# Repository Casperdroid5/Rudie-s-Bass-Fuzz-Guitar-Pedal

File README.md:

# Rudie's Bass Fuzz Guitar Pedal

The Rudie's Bass Fuzz guitar pedal is a unique effect pedal designed to add an interesting twist to the raw sound output of a guitar, particularly bass guitars. With its simple components and construction, it can be replicated for personal use and experimentation.

## Key Features

- **Distinctive Fuzz Effect:** The pedal delivers a powerful and distinctive fuzz effect that adds grit, sustain, and a rich harmonic texture to the guitar's sound. It enhances the overall tone, providing a unique character and vintage vibe to the playing experience.

- **Customizable Controls:** The pedal offers customizable controls, allowing musicians to fine-tune the fuzz effect according to their preferences. Parameters such as gain, tone, and sustain can be adjusted to achieve the desired sound and response.

- **Versatile Usage:** The Bass Fuzz pedal is not limited to bass guitars only. It can also be used with electric guitars and other stringed instruments, providing a wide range of sonic possibilities and expanding the creative options for musicians.

- **True Bypass:** The pedal features true bypass switching, ensuring that the guitar's original signal remains unaltered when the effect is disengaged. This preserves the instrument's natural tone and allows for seamless integration into any setup.

- **Rugged Construction:** The pedal is built with durability in mind. Its sturdy and compact design ensures it can withstand the rigors of live performances and studio sessions. The high-quality components used in its construction contribute to its reliability and longevity.

- **Easy to Use:** The Bass Fuzz pedal is designed for simplicity and ease of use. It features intuitive controls that musicians of all levels can quickly understand and operate. Whether you're a beginner exploring different effects or an experienced player, this pedal is accessible and user-friendly.

- **Personalization and Modification:** The pedal can serve as a starting point for personalization and modification. Musicians can experiment with component substitutions, circuit modifications, or enclosure customization to tailor the pedal's sound and aesthetics to their individual preferences.

- **Open-Source Design:** The Rudie's Bass Fuzz Guitar Pedal is fully open source.

With its distinctive fuzz effect, customizable controls, and robust construction, Rudie's Bass Fuzz Guitar Pedal offers musicians a versatile tool to shape their sound and explore new sonic territories. Its open-source nature encourages creativity, customization, and a collaborative community of musicians and DIY enthusiasts.

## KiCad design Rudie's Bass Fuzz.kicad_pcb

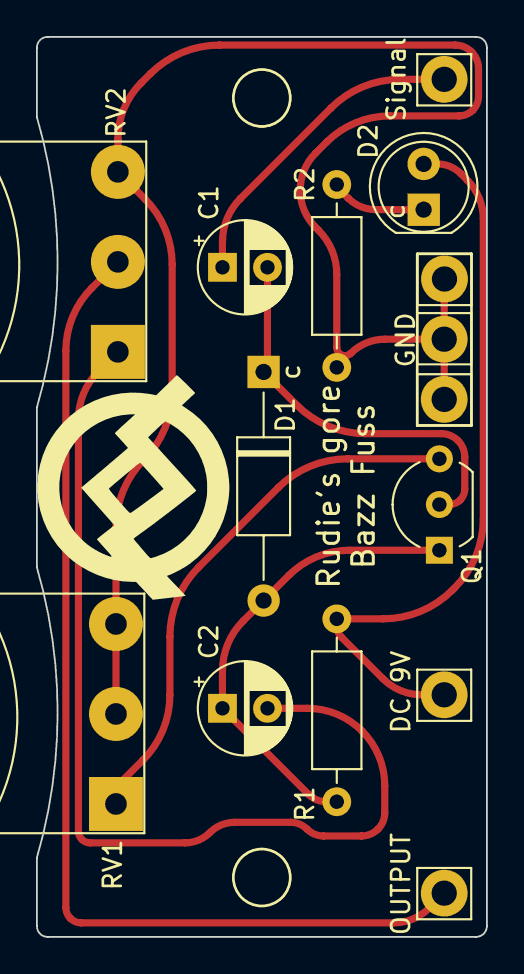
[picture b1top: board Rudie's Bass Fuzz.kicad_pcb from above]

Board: 2 copper layers, 25.0 x 50.0 mm, 19 parts (1 on the bottom side), 9 nets.

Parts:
C1, C2: 47uF; CP_Radial_D5.0mm_P2.50mm
D1: D; D_A-405_P12.70mm_Horizontal
D2: LED; LED_D5.0mm
G1, G2: LOGO
H1, H2: MountingHole; MountingHole_3.2mm_M3
J1, J2, J3, J4, J5, J6: Conn_01x01_Male; Pin_D1.4mm_L8.5mm_W2.8mm_FlatFork
Q1: BC549; TO-92_Inline_Wide
R1: 10K; R_Axial_DIN0207_L6.3mm_D2.5mm_P10.16mm_Horizontal
R2: 470; R_Axial_DIN0207_L6.3mm_D2.5mm_P10.16mm_Horizontal
RV1, RV2: 100K; Potentiometer_Alps_RK163_Single_Horizontal

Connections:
9V: D2.2 (A), J2.1, R1.1
GND: J4.1, J5.1, J6.1, R2.2, RV1.2, RV1.3, RV2.3
unnamed: C1.2, D1.1 (K), Q1.2 (B)
unnamed: C2.1, D1.2 (A), Q1.1 (C), R1.2
unnamed: C2.2, RV2.1
unnamed: D2.1 (K), R2.1
unnamed: Q1.3 (E), RV1.1
Output: J3.1, RV2.2
Signal: C1.1, J1.1

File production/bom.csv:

Designator,Footprint,Quantity,Value,LCSC Part #
"C1, C2",CP_Radial_D5.0mm_P2.50mm,2,47uF,
D1,D_A-405_P12.70mm_Horizontal,1,D,
D2,LED_D5.0mm,1,LED,
"H1, H2",MountingHole_3.2mm_M3,2,MountingHole,
"J1, J2, J3, J4, J5, J6",Pin_D1.4mm_L8.5mm_W2.8mm_FlatFork,6,Conn_01x01_Male,
Q1,TO-92_Inline_Wide,1,BC549,
R1,R_Axial_DIN0207_L6.3mm_D2.5mm_P10.16mm_Horizontal,1,10K,
R2,R_Axial_DIN0207_L6.3mm_D2.5mm_P10.16mm_Horizontal,1,470,
"RV1, RV2",Potentiometer_Alps_RK163_Single_Horizontal,2,100K,

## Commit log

2022-12-13 Original commit
    finished schematic + beginning of board design
    - added indents for potmeters
2022-12-13 aligned components
2022-12-13 rounded corners
2022-12-13 changed potmeter orientation in 3d model
2022-12-13 added power LED
2022-12-13 annotated led components
2022-12-14 added led
2022-12-14 added led to pcb design
2022-12-14 improved silkscreen
2022-12-15 Added logo's + text to Bsilk
2022-12-15 removed wires and added extra gnd pins
2022-12-15 New wiring (ticker traces)
2022-12-15 Single layer PCB
2022-12-15 V0.1 Finished
2022-12-15 moved connectors inwards a bit and added rounded design
2022-12-15 Finalized design
    Improved silkscreen and tracks a bit.
2022-12-15 added bom and production kit
2022-12-15 silkscreen cleanup
2022-12-15 repo cleanup
2022-12-15 added 3d models
2022-12-15 corrected spelling mistake
    bazz fuzz -> bazz fuss (joke)
2023-01-09 Cleanup and added PDF
2023-05-24 add pictures and video
